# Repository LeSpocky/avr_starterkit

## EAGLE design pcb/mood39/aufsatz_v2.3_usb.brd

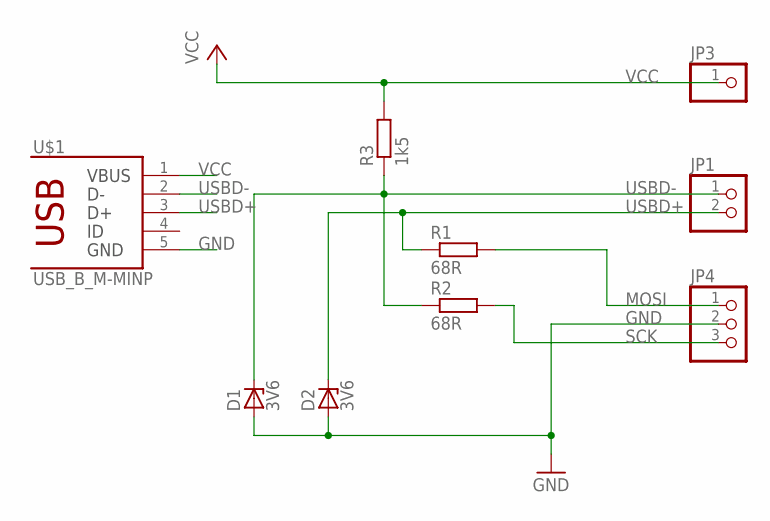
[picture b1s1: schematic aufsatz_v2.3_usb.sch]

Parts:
D1, D2: 3V6; SOD80C
JP1: PINHD-1X2; 1X02
JP3: PINHD-1X1; 1X01
JP4: PINHD-1X3; 1X03
R1, R2: 68R; R0805
R3: 1k5; R0805
U$1: USB_B_M-MINP; USB_B_MINI-PRINT

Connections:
GND: D1.A, D2.A, JP4.2, U$1.5
MOSI: JP4.1, R1.2
SCK: JP4.3, R2.2
USBD+: D2.C, JP1.2, R1.1, U$1.3
USBD-: D1.C, JP1.1, R2.1, R3.1, U$1.2
VCC: JP3.1, R3.2, U$1.1

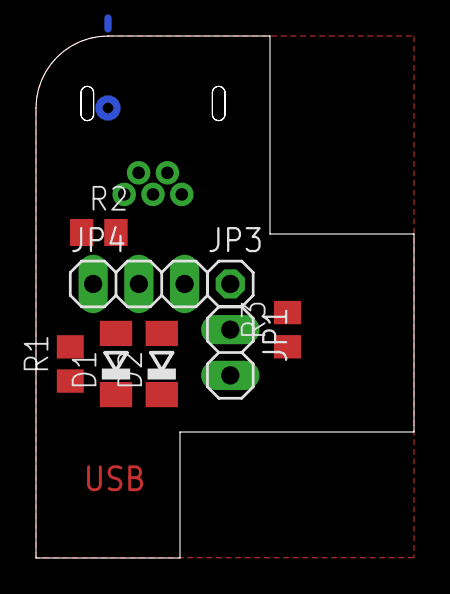
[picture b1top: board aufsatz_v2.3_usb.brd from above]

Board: 2 copper layers, 21.0 x 29.0 mm, 9 parts (1 on the bottom side), 6 nets.

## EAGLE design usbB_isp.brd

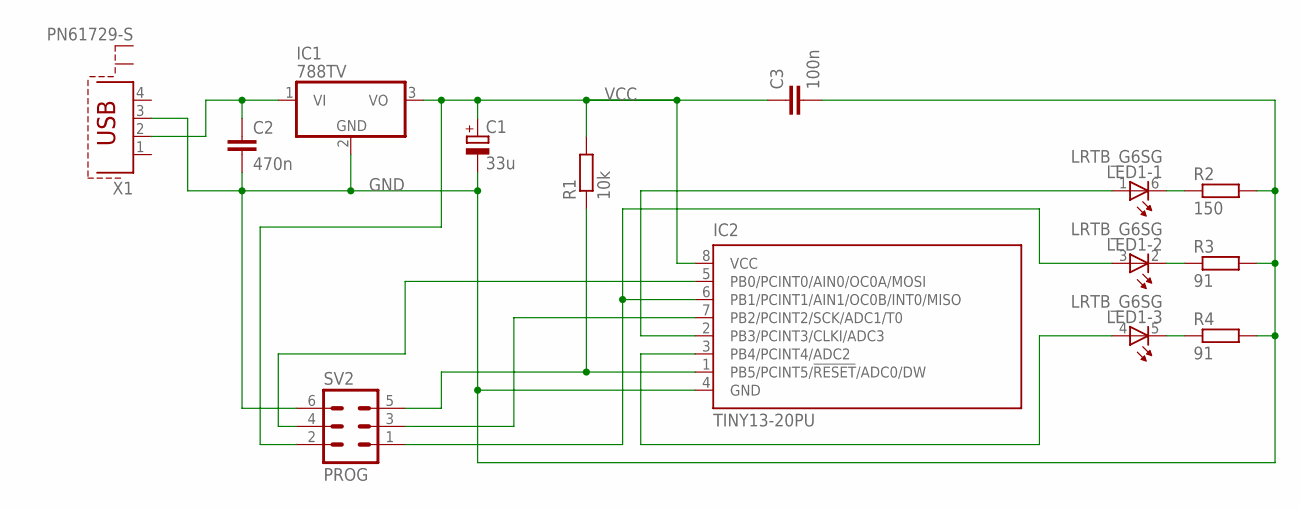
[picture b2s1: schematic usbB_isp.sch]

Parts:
C1: 33u; E2,5-6E
C2: 470n; C050-025X075
C3: 100n; C050-025X075
IC1: 788TV; TO220V
IC2: TINY13-20PU; DIL08
LED1: LRTB_G6SG
R1: 10k; 0204/7
R2: 150; 0204/7
R3, R4: 91; 0204/7
SV2: PROG; ML6
X1: PN61729-S

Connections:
GND: C1.-, C2.2, C3.2, IC1.2 (GND), IC2.4 (GND), R2.2, R3.2, R4.2, SV2.6, X1.3
MISO: IC2.6 (PB1/PCINT1/AIN1/OC0B/INT0/MISO), LED1.3 (A), SV2.1
MOSI: IC2.5 (PB0/PCINT0/AIN0/OC0A/MOSI), SV2.4
unnamed: C2.1, IC1.1 (VI), X1.2
unnamed: IC2.2 (PB3/PCINT3/CLKI/ADC3), LED1.1 (A)
unnamed: LED1.5 (C), R4.1
unnamed: LED1.2 (C), R3.1
unnamed: LED1.6 (C), R2.1
unnamed: IC2.3 (PB4/PCINT4/ADC2), LED1.4 (A)
SCK: IC2.7 (PB2/PCINT2/SCK/ADC1/T0), SV2.3
VCC: C1.+, C3.1, IC1.3 (VO), IC2.8 (VCC), R1.2, SV2.2
_RESET: IC2.1 (PB5/PCINT5/!RESET!/ADC0/DW), R1.1, SV2.5

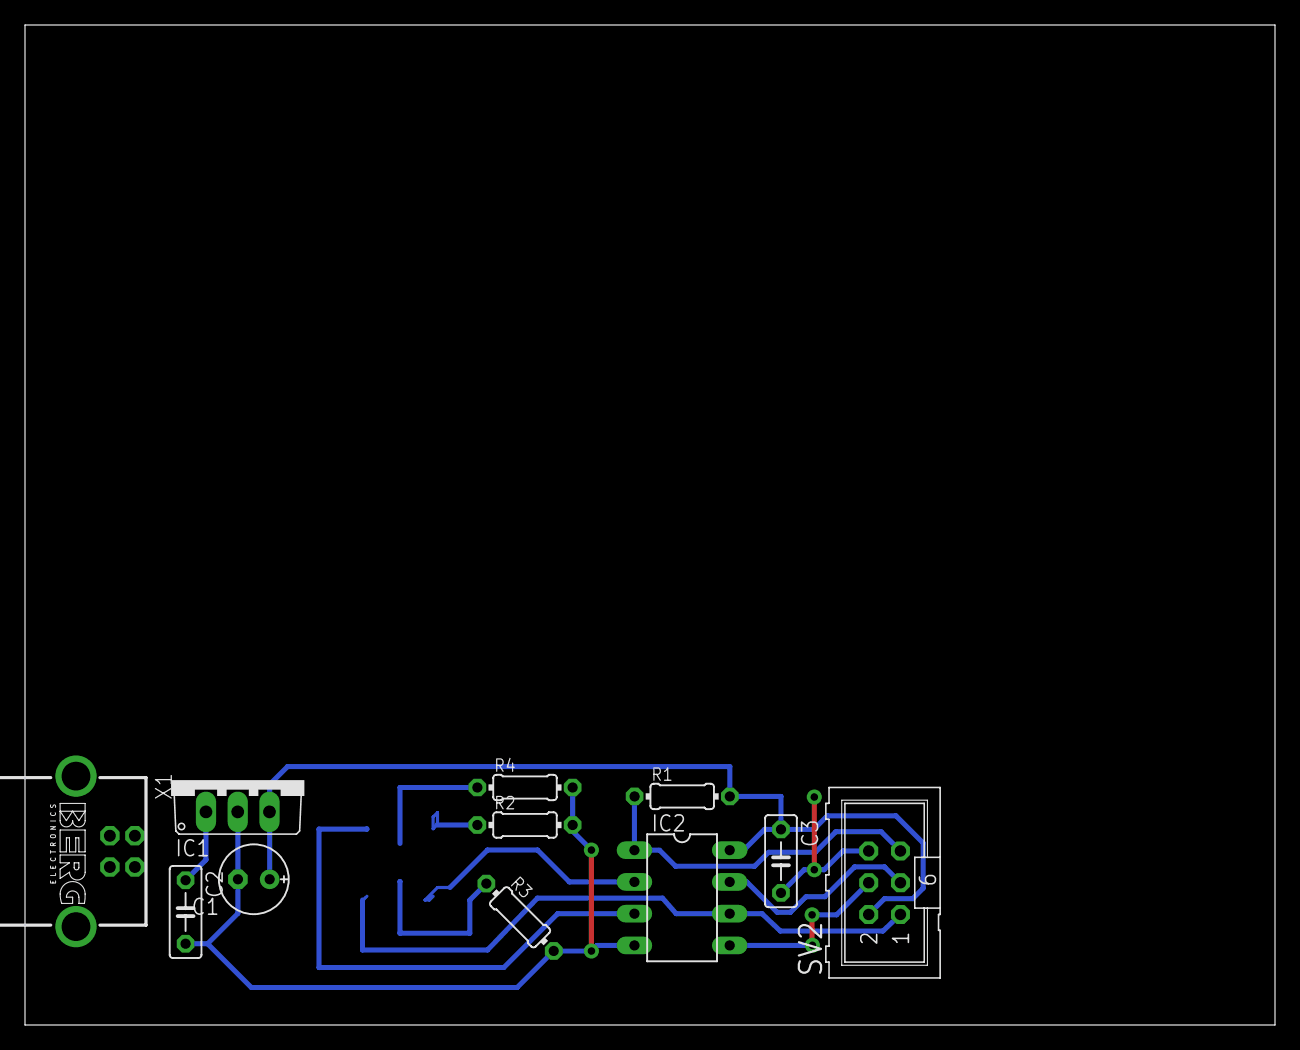
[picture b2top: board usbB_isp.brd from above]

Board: 2 copper layers, 100.0 x 80.0 mm, 12 parts (1 on the bottom side), 12 nets.

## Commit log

2013-03-03 reroute, using 16 mil wires
2013-03-04 adapted design rules and fixed some design rule check issues
2014-02-18 replace mini usb connector
